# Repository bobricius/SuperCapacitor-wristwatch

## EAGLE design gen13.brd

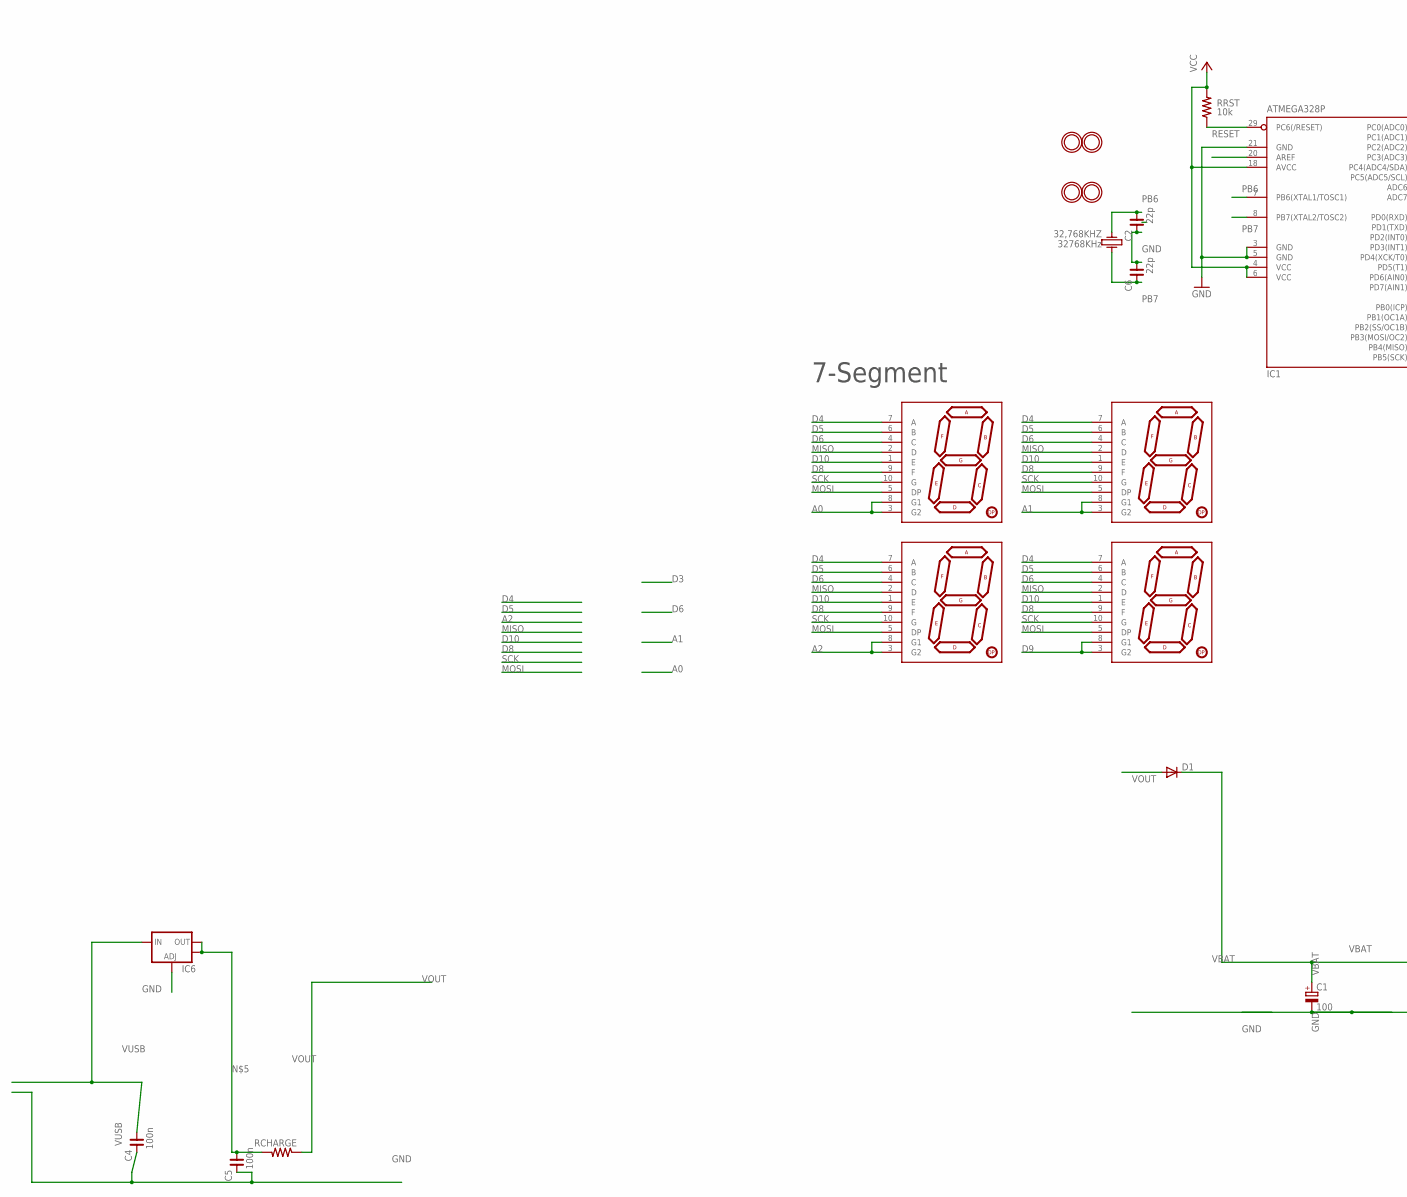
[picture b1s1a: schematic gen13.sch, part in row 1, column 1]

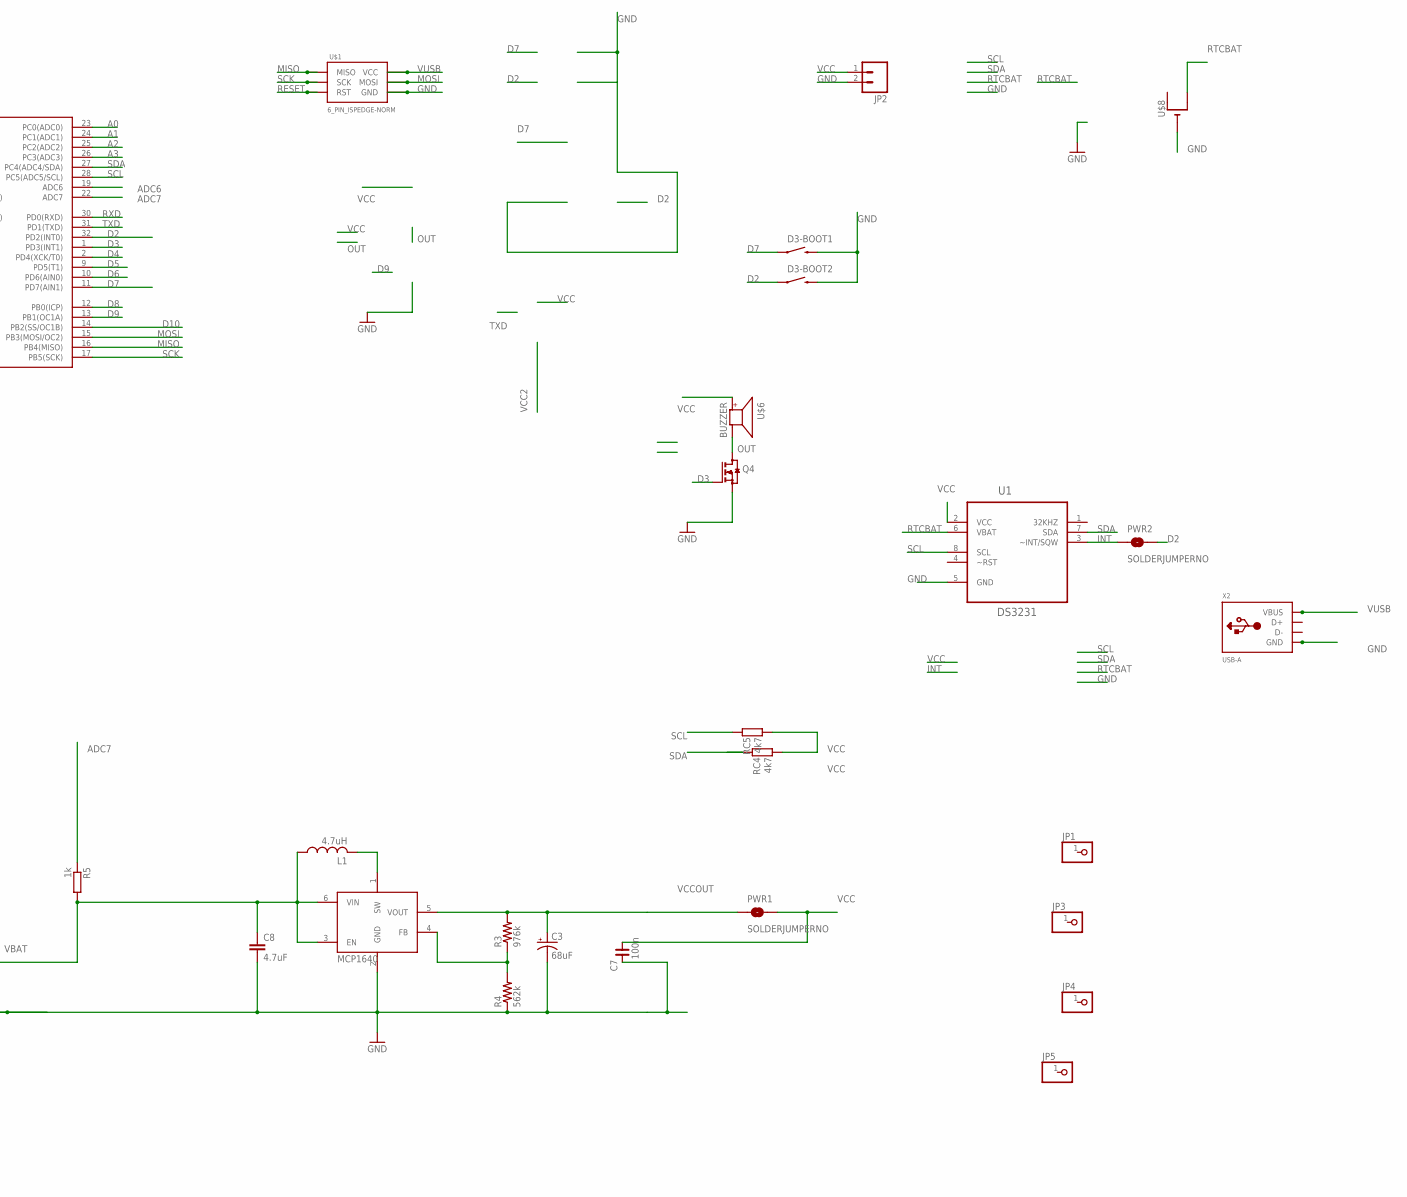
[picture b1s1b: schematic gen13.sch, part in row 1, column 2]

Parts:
32,768KHZ: 32768KHz; KX-327LT
C1: 100; TT2D4
C2, C6: 22p; C0603
C3: 68uF; EIA3216
C4, C5, C7: 100n; C0603
C8: 4.7uF; 0805
D1: DIODE-DO214AC; DO214AC
D3-BOOT1, D3-BOOT2: SWITCH-MOMENTARY-2-SMD-1101NE; TACTILE-SWITCH-1101NE
DIG1, DIG2, DIG3, DIG4: 7-SEGMENT-DISPLAY-1"-RED; 7-SEGMENT-SMD
IC1: ATMEGA328P; TQFP32-08
IC6: V_REG_LM1117SOT223; SOT223
JP1, JP3, JP4, JP5: PINHD-1X1; 1X01
JP2: M02PTH; 1X02
L1: 4.7uH; LQH44
PWR1, PWR2: SOLDERJUMPERNO; SJ_2S-NO
Q4: BSS123; SOT23
R3: 976k; 0603-RES
R4: 562k; 0603-RES
R5: 1k; R0603
RC4, RC5: 4k7; R0603
RCHARGE: RESISTOR1206; 1206
RRST: 10k; R0603@1
U1: DS3231; SOIC8_150MIL
U2: MCP1640; SOT23-6
U$1: 6_PIN_ISPEDGE-NORM; 6_PIN_EDGE
U$2, U$3, U$4, U$5: MOUNTINGHOLE2.0; MOUNTINGHOLE_2.0_PLATED
U$6: BUZZER; SMT-8585-BUZZER
U$8: CR1220SMT; CR1220-SMD
X2: USB-A; MOLEX_480371000

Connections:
A0: DIG1.3 (G2), DIG1.8 (G1), IC1.23 (PC0(ADC0))
A1: DIG2.3 (G2), DIG2.8 (G1), IC1.24 (PC1(ADC1))
A2: DIG3.3 (G2), DIG3.8 (G1), IC1.25 (PC2(ADC2))
A3: IC1.26 (PC3(ADC3))
ADC6: IC1.19 (ADC6)
ADC7: IC1.22 (ADC7), R5.1
AREF: IC1.20 (AREF)
D2: D3-BOOT2.P$1 (1), IC1.32 (PD2(INT0)), PWR2.2
D3: IC1.1 (PD3(INT1)), Q4.1 (G)
D4: DIG1.7 (A), DIG2.7 (A), DIG3.7 (A), DIG4.7 (A), IC1.2 (PD4(XCK/T0))
D5: DIG1.6 (B), DIG2.6 (B), DIG3.6 (B), DIG4.6 (B), IC1.9 (PD5(T1))
D6: DIG1.4 (C), DIG2.4 (C), DIG3.4 (C), DIG4.4 (C), IC1.10 (PD6(AIN0))
D7: D3-BOOT1.P$1 (1), IC1.11 (PD7(AIN1))
D8: DIG1.9 (F), DIG2.9 (F), DIG3.9 (F), DIG4.9 (F), IC1.12 (PB0(ICP))
D9: DIG4.3 (G2), DIG4.8 (G1), IC1.13 (PB1(OC1A))
D10: DIG1.1 (E), DIG2.1 (E), DIG3.1 (E), DIG4.1 (E), IC1.14 (PB2(SS/OC1B))
GND: C1.-, C2.2, C3.C (-), C4.2, C5.2, C6.1, C7.2, C8.2, D3-BOOT1.P$2 (2), D3-BOOT2.P$2 (2), IC1.3 (GND), IC1.5 (GND), IC1.21 (GND), IC6.1 (ADJ), JP2.2, Q4.2 (S), R4.1, U1.5 (GND), U2.2 (GND), U$1.6 (GND), U$8.-, X2.4 (GND)
INT: PWR2.1, U1.3 (~INT/SQW)
MISO: DIG1.2 (D), DIG2.2 (D), DIG3.2 (D), DIG4.2 (D), IC1.16 (PB4(MISO)), U$1.1 (MISO)
MOSI: DIG1.5 (DP), DIG2.5 (DP), DIG3.5 (DP), DIG4.5 (DP), IC1.15 (PB3(MOSI/OC2)), U$1.4 (MOSI)
unnamed: L1.P$2 (2), U2.1 (SW)
unnamed: C5.1, IC6.2 (OUT), IC6.4 (OUT), RCHARGE.2
unnamed: R3.1, R4.2, U2.4 (FB)
OUT: Q4.3 (D), U$6.-
PB6: 32,768KHZ.4, C2.1, IC1.7 (PB6(XTAL1/TOSC1))
PB7: 32,768KHZ.1, C6.2, IC1.8 (PB7(XTAL2/TOSC2))
RESET: IC1.29 (PC6(/RESET)), RRST.1, U$1.5 (RST)
RTCBAT: U1.6 (VBAT), U$8.+$2 (+1)
RXD: IC1.30 (PD0(RXD))
SCK: DIG1.10 (G), DIG2.10 (G), DIG3.10 (G), DIG4.10 (G), IC1.17 (PB5(SCK)), U$1.3 (SCK)
SCL: IC1.28 (PC5(ADC5/SCL)), RC5.2, U1.8 (SCL)
SDA: IC1.27 (PC4(ADC4/SDA)), RC4.2, U1.7 (SDA)
TXD: IC1.31 (PD1(TXD))
VBAT: C1.+, C8.1, D1.C, L1.P$1 (1), R5.2, U2.3 (EN), U2.6 (VIN)
VCC: C7.1, IC1.4 (VCC), IC1.6 (VCC), IC1.18 (AVCC), JP2.1, PWR1.2, RC4.1, RC5.1, RRST.2, U1.2 (VCC), U$6.+
VCCOUT: C3.A (+), PWR1.1, R3.2, U2.5 (VOUT)
VOUT: D1.A, RCHARGE.1
VUSB: C4.1, IC6.3 (IN), U$1.2 (VCC), X2.1 (VBUS)

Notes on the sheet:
7-Segment

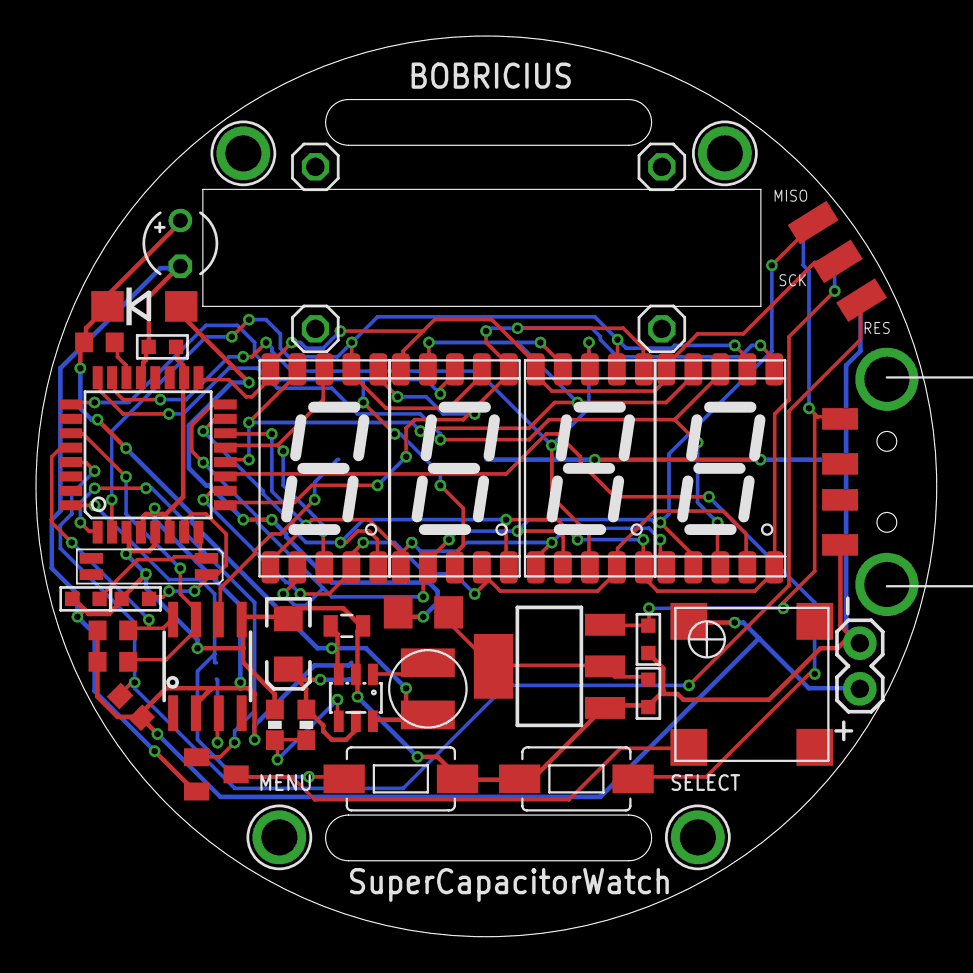
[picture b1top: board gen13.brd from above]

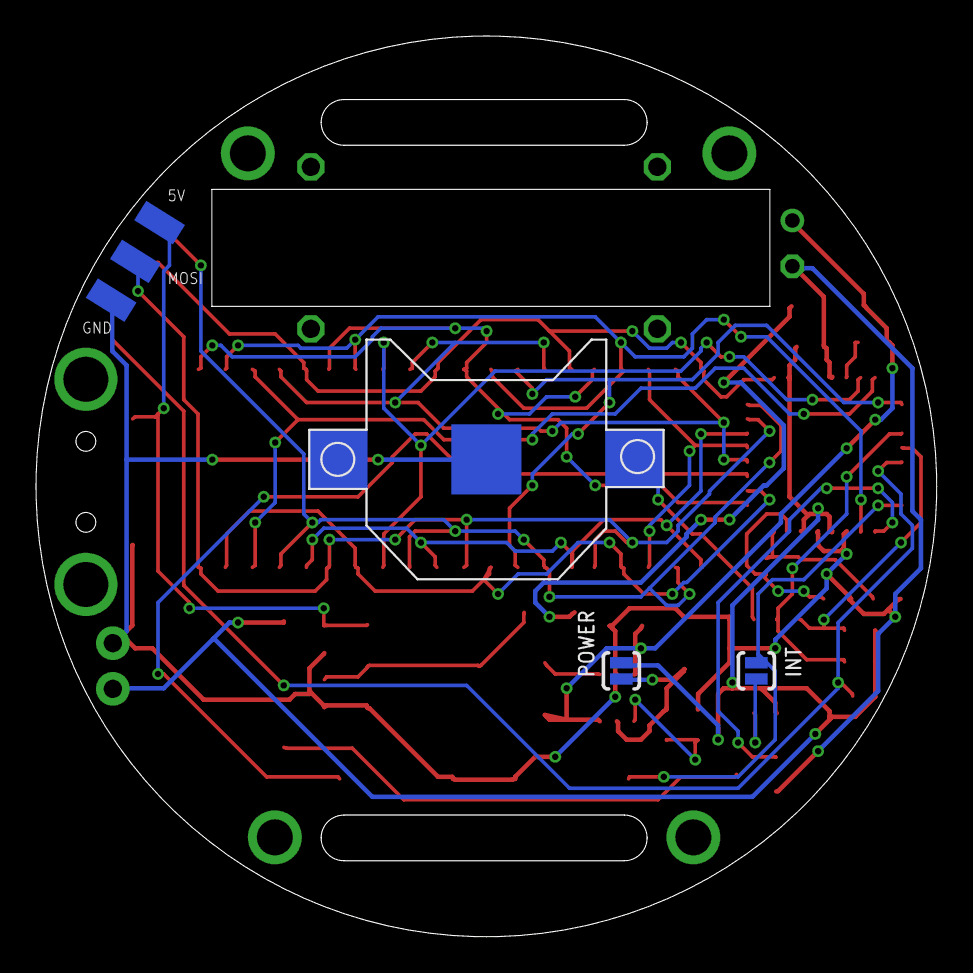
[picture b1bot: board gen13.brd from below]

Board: 2 copper layers, 50.0 x 50.0 mm, 44 parts (3 on the bottom side), 33 nets.

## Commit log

2015-08-05 :circus_tent: Added .gitattributes & .gitignore files
2015-08-05 First upload

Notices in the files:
parts and their libraries:
SparkFun: Licensing: CC v3.0 Share-Alike You are welcome to use this library for commercial purposes.
SparkFun-Connectors: Licensing: Creative Commons ShareAlike 4.0 International - https://creativecommons.org/licenses/by-sa/4.0
